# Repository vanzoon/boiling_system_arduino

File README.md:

Система для автоматизации водонагревательного бака. Первый учебный, но работающий проект, прототип, на
Ардуинке. Сделан под чаёк в зимние вечера 21 года) В KiCad cоставлена электрическая схема ко всему этому добру 
Много чего стоит исправить/улучшить, например развести печатную плату или
попробовать отрефакторить код на использование прерываний
Для себя позже добавлю уточняющие описания, как задач, так и используемой электронной базы
Остальным лучше не уподобляться и не делать подобные системы на ардуине при
желании реального использования дома и тем более в промышленных объектах.
Слишком много неоптимизированного мусора в исходном коде проекта Arduino (да и
моего тоже)) и качество комплектующих (ещё и китайских) дадут о себе знать. Чего
стоят только свежие серии китайских датчиков температуры с реальными откланениями в значениях на 2+
градуса Цельсия при заявленных 0.1 (что на самом деле уже достаточно много).

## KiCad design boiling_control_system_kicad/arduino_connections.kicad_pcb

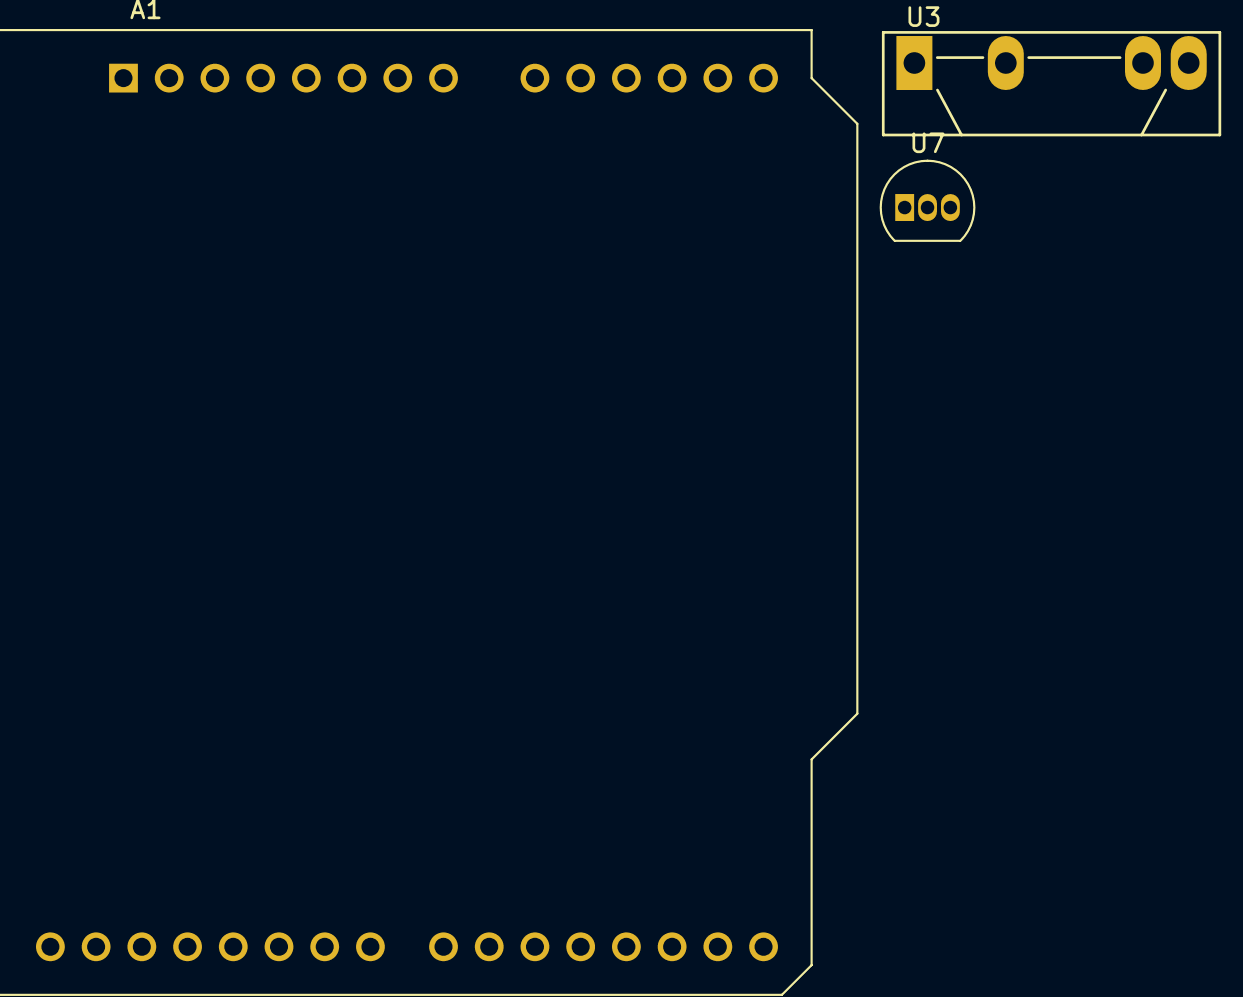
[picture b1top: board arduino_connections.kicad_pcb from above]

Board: 2 copper layers, 3 parts (0 on the bottom side), 4 nets, no tracks yet.

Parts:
A1: Arduino_UNO_R3; Arduino_UNO_R2
U3: SSR-40 DA; SIP4_Sharp-SSR_P7.62mm_Straight
U7: DS18B20; TO-92_Inline

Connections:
GND: A1.6, U3.4, U7.1
unnamed: A1.5, U7.3
unnamed: A1.17, U7.2
unnamed: A1.22, U3.3

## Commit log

2021-04-09 initial
2021-04-09 add README
2021-04-09 fix: kicad project, +archieved
2021-04-12 fix: circuit
